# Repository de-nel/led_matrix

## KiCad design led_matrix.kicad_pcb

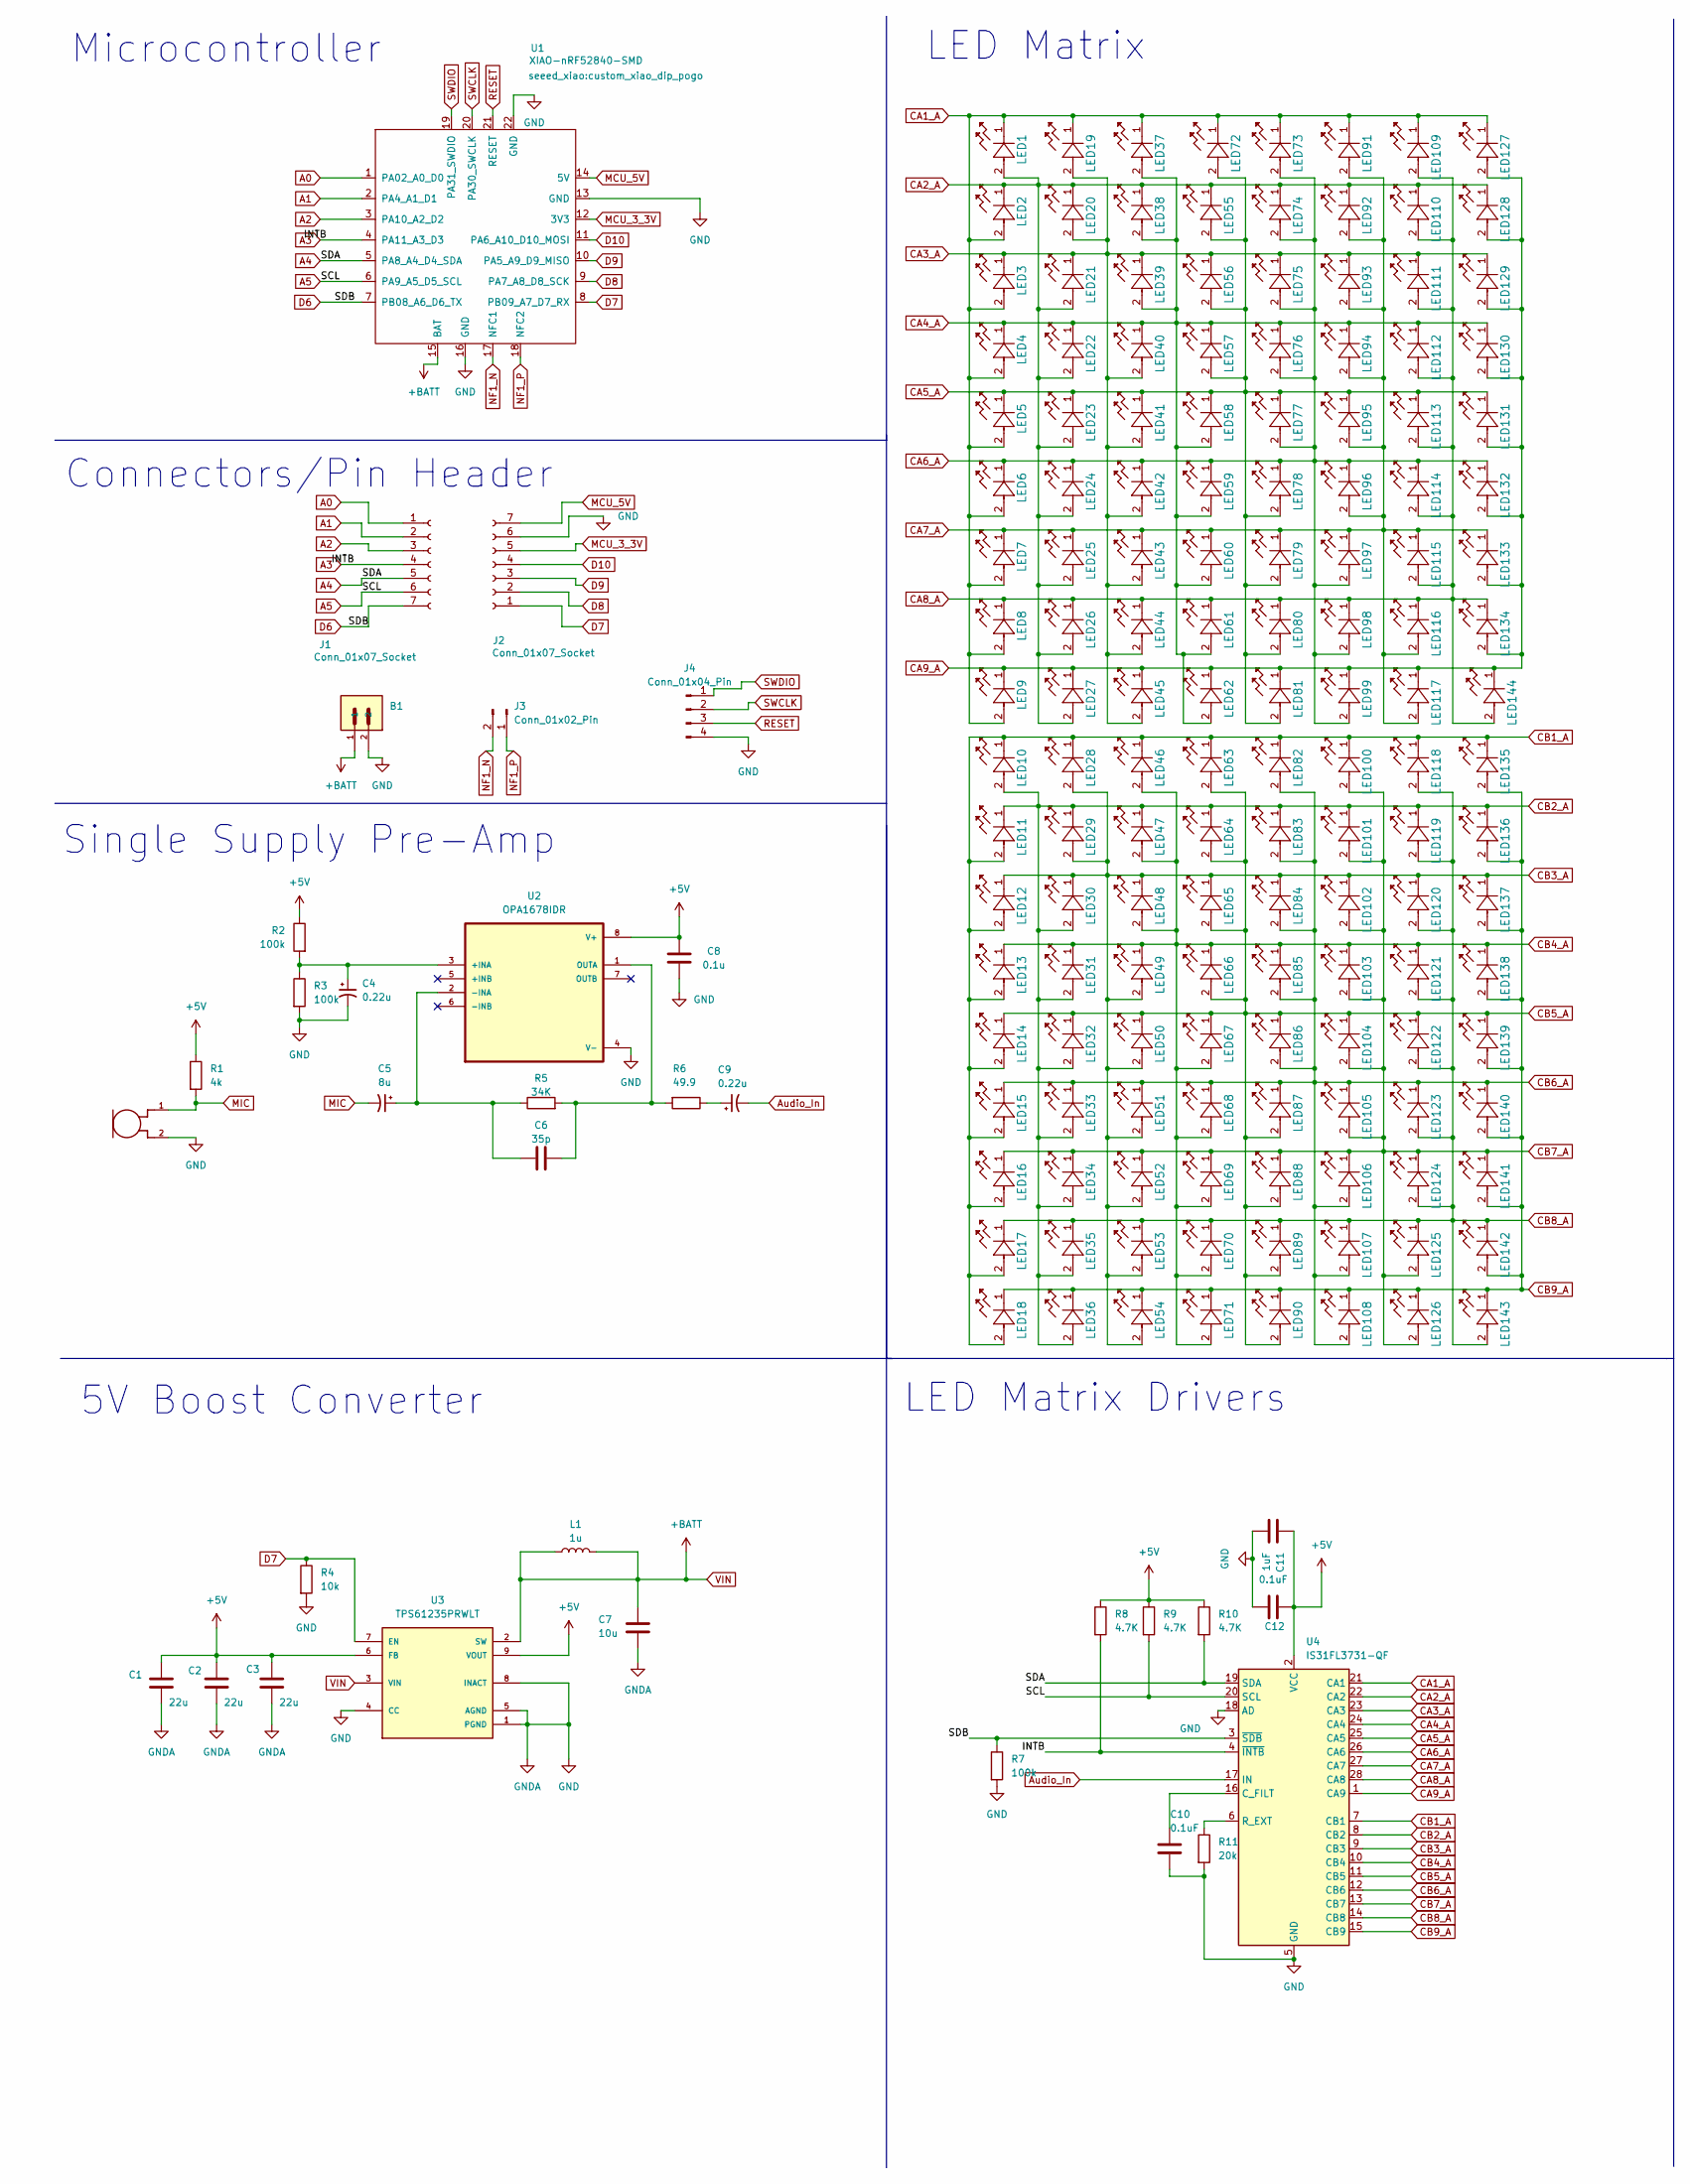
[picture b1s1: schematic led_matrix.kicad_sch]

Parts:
B1: S2B-PH-SM4-TB; JST_S2B-PH-SM4-TB
C1, C2, C3: 22u; C_0805_2012Metric_Pad1.18x1.45mm_HandSolder
C4, C9: 0.22u; CP_EIA-2012-15_AVX-P_HandSolder
C5: 8u; CP_EIA-2012-15_AVX-P_HandSolder
C6: 35p; C_0805_2012Metric_Pad1.18x1.45mm_HandSolder
C7: 10u; C_0805_2012Metric_Pad1.18x1.45mm_HandSolder
C8: 0.1u; C_0805_2012Metric_Pad1.18x1.45mm_HandSolder
C10, C12: 0.1uF; C_0805_2012Metric_Pad1.18x1.45mm_HandSolder
C11: 1uF; C_0805_2012Metric_Pad1.18x1.45mm_HandSolder
J1, J2: Conn_01x07_Socket; PinSocket_1x07_P2.54mm_Vertical_SMD_Pin1Left
J3: Conn_01x02_Pin; SolderWire-0.25sqmm_1x02_P4.5mm_D0.65mm_OD2mm
J4: Conn_01x04_Pin; PinHeader_1x04_P2.54mm_Vertical_SMD_Pin1Left
L1: 1u; L_0805_2012Metric_Pad1.15x1.40mm_HandSolder
LED1, LED2, LED3, LED4, LED5, LED6, LED7, LED8, LED9, LED10, LED11, LED12, LED13, LED14, LED15, LED16, LED17, LED18, LED19, LED20, LED21, LED22, LED23, LED24, LED25, LED26, LED27, LED28, LED29, LED30, LED31, LED32, LED33, LED34, LED35, LED36, LED37, LED38, LED39, LED40, LED41, LED42, LED43, LED44, LED45, LED46, LED47, LED48, LED49, LED50, LED51, LED52, LED53, LED54, LED55, LED56, LED57, LED58, LED59, LED60, LED61, LED62, LED63, LED64, LED65, LED66, LED67, LED68, LED69, LED70, LED71, LED72, LED73, LED74, LED75, LED76, LED77, LED78, LED79, LED80, LED81, LED82, LED83, LED84, LED85, LED86, LED87, LED88, LED89, LED90, LED91, LED92, LED93, LED94, LED95, LED96, LED97, LED98, LED99, LED100, LED101, LED102, LED103, LED104, LED105, LED106, LED107, LED108, LED109, LED110, LED111, LED112, LED113, LED114, LED115, LED116, LED117, LED118, LED119, LED120, LED121, LED122, LED123, LED124, LED125, LED126, LED127, LED128, LED129, LED130, LED131, LED132, LED133, LED134, LED135, LED136, LED137, LED138, LED139, LED140, LED141, LED142, LED143, LED144: IN-S85AT5B; LED_IN-S85AT5B
M1: CMA-4544PF-W; MIC_CMA-4544PF-W
R1: 4k; R_0805_2012Metric_Pad1.20x1.40mm_HandSolder
R2, R3, R7: 100k; R_0805_2012Metric_Pad1.20x1.40mm_HandSolder
R4: 10k; R_0805_2012Metric_Pad1.20x1.40mm_HandSolder
R5: 34K; LED_0805_2012Metric_Pad1.15x1.40mm_HandSolder
R6: 49.9; R_0805_2012Metric_Pad1.20x1.40mm_HandSolder
R8, R9, R10: 4.7K; R_0805_2012Metric_Pad1.20x1.40mm_HandSolder
R11: 20k; R_0805_2012Metric_Pad1.20x1.40mm_HandSolder
U1: XIAO-nRF52840-SMD; custom_xiao_dip_pogo
U2: OPA1678IDR; SOIC127P599X175-8N
U3: TPS61235PRWLT; CONV_TPS61235PRWLT
U4: IS31FL3731-QF; QFN40P400X400X80-29N-D

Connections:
+5V: C1.1, C2.1, C3.1, C8.1, C11.1, C12.1, R1.1, R2.1, R8.1, R9.1, R10.1, U2.8 (V+), U3.6 (FB), U3.9 (VOUT), U4.2 (VCC)
A0: J1.1, U1.1 (PA02_A0_D0)
A1: J1.2, U1.2 (PA4_A1_D1)
A2: J1.3, U1.3 (PA10_A2_D2)
A3: J1.4, R8.2, U1.4 (PA11_A3_D3), U4.4 (~INTB)
A4: J1.5, R10.2, U1.5 (PA8_A4_D4_SDA), U4.19 (SDA)
A5: J1.6, R9.2, U1.6 (PA9_A5_D5_SCL), U4.20 (SCL)
Audio_In: C9.2, U4.17 (IN)
CA1_A: LED1.1, LED2.2, LED3.2, LED4.2, LED5.2, LED6.2, LED7.2, LED8.2, LED9.2, LED19.1, LED37.1, LED72.1, LED73.1, LED91.1, LED109.1, LED127.1, U4.21 (CA1)
CA2_A: LED1.2, LED2.1, LED20.1, LED21.2, LED22.2, LED23.2, LED24.2, LED25.2, LED26.2, LED27.2, LED38.1, LED55.1, LED74.1, LED92.1, LED110.1, LED128.1, U4.22 (CA2)
CA3_A: LED3.1, LED19.2, LED20.2, LED21.1, LED39.1, LED40.2, LED41.2, LED42.2, LED43.2, LED44.2, LED45.2, LED56.1, LED75.1, LED93.1, LED111.1, LED129.1, U4.23 (CA3)
CA4_A: LED4.1, LED22.1, LED37.2, LED38.2, LED39.2, LED40.1, LED57.1, LED58.2, LED59.2, LED60.2, LED61.2, LED62.2, LED76.1, LED94.1, LED112.1, LED130.1, U4.24 (CA4)
CA5_A: LED5.1, LED23.1, LED41.1, LED55.2, LED56.2, LED57.2, LED58.1, LED72.2, LED77.1, LED78.2, LED79.2, LED80.2, LED81.2, LED95.1, LED113.1, LED131.1, U4.25 (CA5)
CA6_A: LED6.1, LED24.1, LED42.1, LED59.1, LED73.2, LED74.2, LED75.2, LED76.2, LED77.2, LED78.1, LED96.1, LED97.2, LED98.2, LED99.2, LED114.1, LED132.1, U4.26 (CA6)
CA7_A: LED7.1, LED25.1, LED43.1, LED60.1, LED79.1, LED91.2, LED92.2, LED93.2, LED94.2, LED95.2, LED96.2, LED97.1, LED115.1, LED116.2, LED117.2, LED133.1, U4.27 (CA7)
CA8_A: LED8.1, LED26.1, LED44.1, LED61.1, LED80.1, LED98.1, LED109.2, LED110.2, LED111.2, LED112.2, LED113.2, LED114.2, LED115.2, LED116.1, LED134.1, LED144.2, U4.28 (CA8)
CA9_A: LED9.1, LED27.1, LED45.1, LED62.1, LED81.1, LED99.1, LED117.1, LED127.2, LED128.2, LED129.2, LED130.2, LED131.2, LED132.2, LED133.2, LED134.2, LED144.1, U4.1 (CA9)
CB1_A: LED10.1, LED11.2, LED12.2, LED13.2, LED14.2, LED15.2, LED16.2, LED17.2, LED18.2, LED28.1, LED46.1, LED63.1, LED82.1, LED100.1, LED118.1, LED135.1, U4.7 (CB1)
CB2_A: LED10.2, LED11.1, LED29.1, LED30.2, LED31.2, LED32.2, LED33.2, LED34.2, LED35.2, LED36.2, LED47.1, LED64.1, LED83.1, LED101.1, LED119.1, LED136.1, U4.8 (CB2)
CB3_A: LED12.1, LED28.2, LED29.2, LED30.1, LED48.1, LED49.2, LED50.2, LED51.2, LED52.2, LED53.2, LED54.2, LED65.1, LED84.1, LED102.1, LED120.1, LED137.1, U4.9 (CB3)
CB4_A: LED13.1, LED31.1, LED46.2, LED47.2, LED48.2, LED49.1, LED66.1, LED67.2, LED68.2, LED69.2, LED70.2, LED71.2, LED85.1, LED103.1, LED121.1, LED138.1, U4.10 (CB4)
CB5_A: LED14.1, LED32.1, LED50.1, LED63.2, LED64.2, LED65.2, LED66.2, LED67.1, LED86.1, LED87.2, LED88.2, LED89.2, LED90.2, LED104.1, LED122.1, LED139.1, U4.11 (CB5)
CB6_A: LED15.1, LED33.1, LED51.1, LED68.1, LED82.2, LED83.2, LED84.2, LED85.2, LED86.2, LED87.1, LED105.1, LED106.2, LED107.2, LED108.2, LED123.1, LED140.1, U4.12 (CB6)
CB7_A: LED16.1, LED34.1, LED52.1, LED69.1, LED88.1, LED100.2, LED101.2, LED102.2, LED103.2, LED104.2, LED105.2, LED106.1, LED124.1, LED125.2, LED126.2, LED141.1, U4.13 (CB7)
CB8_A: LED17.1, LED35.1, LED53.1, LED70.1, LED89.1, LED107.1, LED118.2, LED119.2, LED120.2, LED121.2, LED122.2, LED123.2, LED124.2, LED125.1, LED142.1, LED143.2, U4.14 (CB8)
CB9_A: LED18.1, LED36.1, LED54.1, LED71.1, LED90.1, LED108.1, LED126.1, LED135.2, LED136.2, LED137.2, LED138.2, LED139.2, LED140.2, LED141.2, LED142.2, LED143.1, U4.15 (CB9)
D6: J1.7, R7.1, U1.7 (PB08_A6_D6_TX), U4.3 (~SDB)
D7: J2.1, R4.1, U1.8 (PB09_A7_D7_RX), U3.7 (EN)
D8: J2.2, U1.9 (PA7_A8_D8_SCK)
D9: J2.3, U1.10 (PA5_A9_D9_MISO)
D10: J2.4, U1.11 (PA6_A10_D10_MOSI)
GND: B1.2, C1.2, C2.2, C3.2, C4.2, C7.2, C8.2, C10.2, C11.2, C12.2, J2.6, J4.4, M1.2, R3.2, R4.2, R7.2, R11.2, U1.13 (GND), U1.16 (GND), U1.22 (GND), U2.4 (V-), U3.1 (PGND), U3.4 (CC), U3.5 (AGND), U3.8 (INACT), U4.5 (GND), U4.18 (AD), U4.29 (GND)
MCU_3_3V: J2.5, U1.12 (3V3)
MCU_5V: J2.7, U1.14 (5V)
MIC: C5.2, M1.1, R1.2
NF1_N: J3.2, U1.17 (NFC1)
NF1_P: J3.1, U1.18 (NFC2)
unnamed: C9.1, R6.1
unnamed: C4.1, R2.2, R3.1, U2.3 (+INA)
unnamed: C5.1, C6.1, R5.1, U2.2 (-INA)
unnamed: C6.2, R5.2, R6.2, U2.1 (OUTA)
unnamed: C10.1, U4.16 (C_FILT)
unnamed: R11.1, U4.6 (R_EXT)
RESET: J4.3, U1.21 (RESET)
SWCLK: J4.2, U1.20 (PA30_SWCLK)
SWDIO: J4.1, U1.19 (PA31_SWDIO)
VIN: B1.1, C7.1, L1.1, L1.2, U1.15 (BAT), U3.2 (SW), U3.3 (VIN)

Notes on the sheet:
LED Matrix Drivers
LED Matrix
Microcontroller
Single Supply Pre-Amp
Connectors/Pin Header
5V Boost Converter

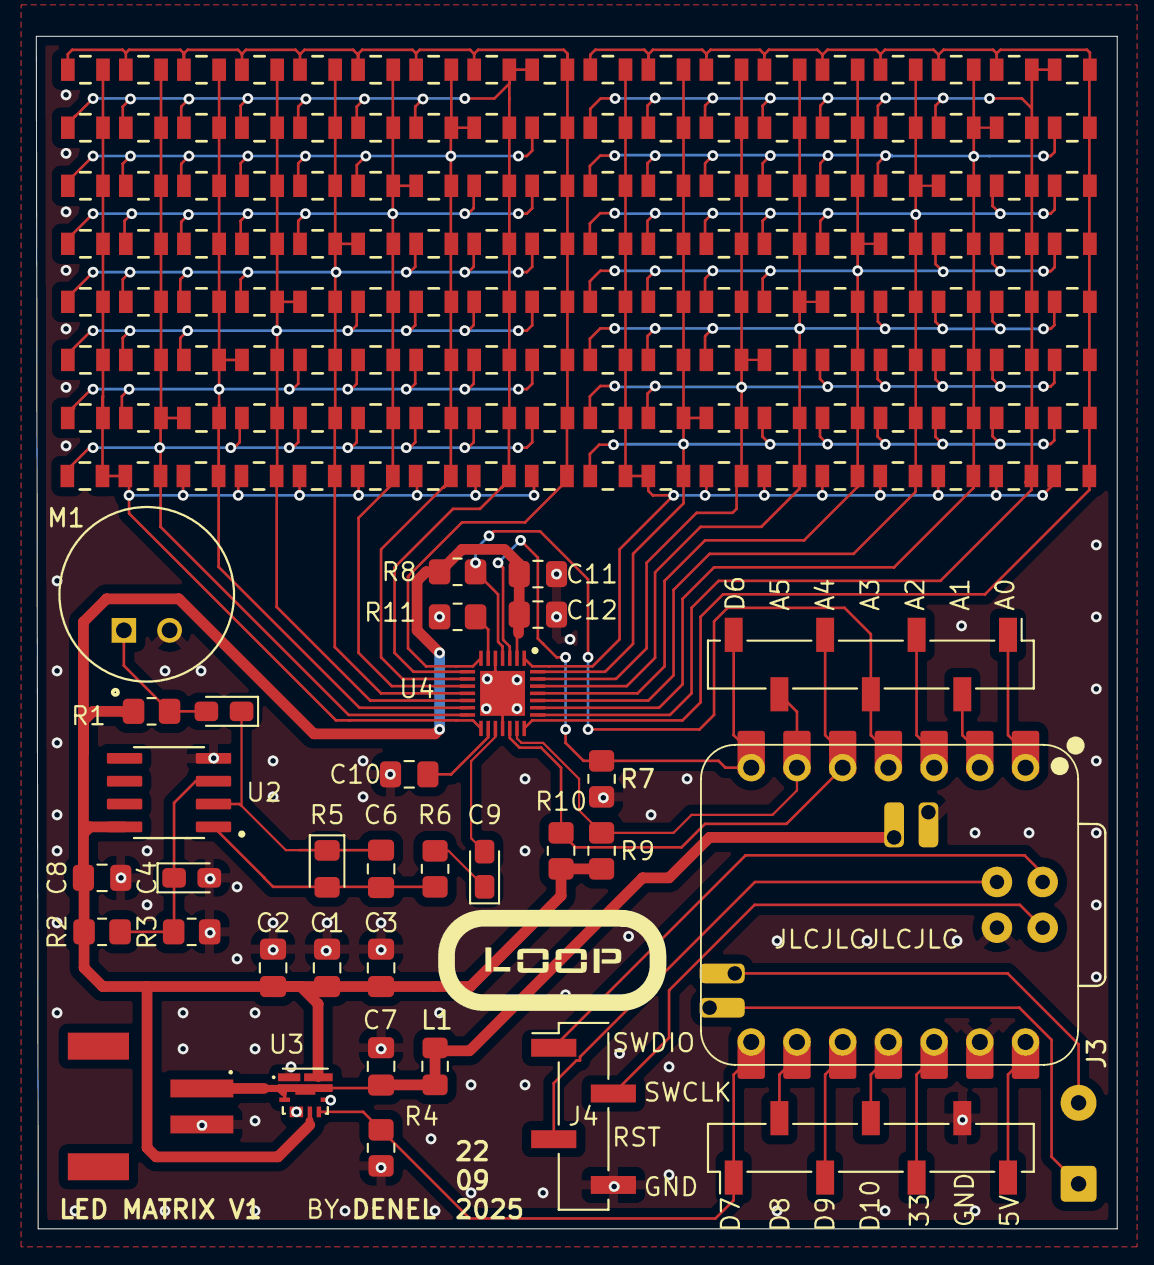
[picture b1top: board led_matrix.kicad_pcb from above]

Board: 2 copper layers, 60.1 x 66.2 mm, 178 parts (0 on the bottom side), 47 nets.

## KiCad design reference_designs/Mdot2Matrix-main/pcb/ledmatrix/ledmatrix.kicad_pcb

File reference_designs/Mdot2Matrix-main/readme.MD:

# M.2 LED Matrix

## Goal

This project is a showcase and starting point for M.2 PCIe hardware. The interface chip CH382 was used to inteface between the first PCIe lane and the CH32V208 MCU over UART.
Check out the [versionProject video](https://youtu.be/yxVQkL01FD4)

## State

RTS and DTR control flow signals are used to put the MCU into bootloader. !Caution This version is not working correctly as the signals are flipped on boot etc. Here is an updated [version](https://www.falstad.com/circuit/circuitjs.html?ctz=CQAgjCAMB0l3BWcAOaAmA7MgnGB-kA2MAFgwTREMJCQUloFMBaMMAKACcQS4QBmSCVoYag4QzDxIXETWaFhCUQKFQQaaewDmA5MLBj9AygxmaMGtAbTIrw5A2EAlACoBldhZ4k7C4SS+IKxglMIAhAAirs7sAO56wv4+fopQsvzGIZSZSWmSWt5o1sFBxUnYNMLRsc6JwWw5WaQS6rwC0PzqZtAIXpCWgXYtKSCVPCAAQgDy067mA1QIYmqEyxrrwgByzu6uOvXWDLkbNGYZFKV2tn5BBfAXlKHXyMO26lIPAC4Cl8xBJ3+dkkUF69EIkAhyDAlTQFAwlhgCEqhFwkLQhGscOIqhAABNGAAzACGAFcADZfdg-fiXZ71ekgpH4NBgZC2QykBGhUEIEjUQg4fS5MhdQT4olkynxBmBUYjGQJcrgd7K8TpBJDYJpZTyfLsAAy4DlQLG8ju4BAJPJAGdGB0ujIjSN6eNGZbrXaHekALIgDCaVTCUR2dWSaBrdh4+xBnh8dVPLbKUIZYxHBnYUzgaQyP1aka+SRy8ORzVBZJa-VluxpE5V+q14yNdI241JMolU1mK3E22MR7gMR-C2fODsVsu1Uld0MT39pXT1WvFXAgcwnJ0973McJXWxtYrCTsfiCpaHs8CE-dY+n-Ny-Mqc4JA+xgPHNQyVtv1+Bk-Aj29naBzfn+-q-sY5wAMZyLGe6gQYLCWGgsCQLgoSspg+jIBgeCgnAEAyLocGnnBEEahoy6msqXYyrSTxGAYZy0Vk-BNIx5EnCMnGZhxdI8dxpjsAAHhRlisMctLBIMKogAAqj6AASbBbOwABGGg4dqdi8AwgYyCJNyDkg-BXoY2kyfJSlgCp6mYBAUiDHwMJIDIAD2YwgP+JBSKY0B4JiLkoXA2CiMscLqJQ2ACFMszzOw7lSJ5bQ+bQeHwCFB7hbp2bRTsezxf6SVOClgUERohVdDUBVdF5JWgmVOTRW4nhAA)

In general the interface chip draws 170mA which puts the little LDO at it's limit. The thermals are terrible. Would not recomment to use this setup for a commercial project without a severe refinement.

## Tools

The firmware can be uploaded via the [wch web isp](https://github.com/basilhussain/wch-web-isp)

The code is written with the [MounRiver Studio](http://www.mounriver.com/download)

Node.js is required to run the websocket server

## Vibe coding

The majority of the web tool and the server are generated with ChatGPT which was trained on dacades of mine and your public code.

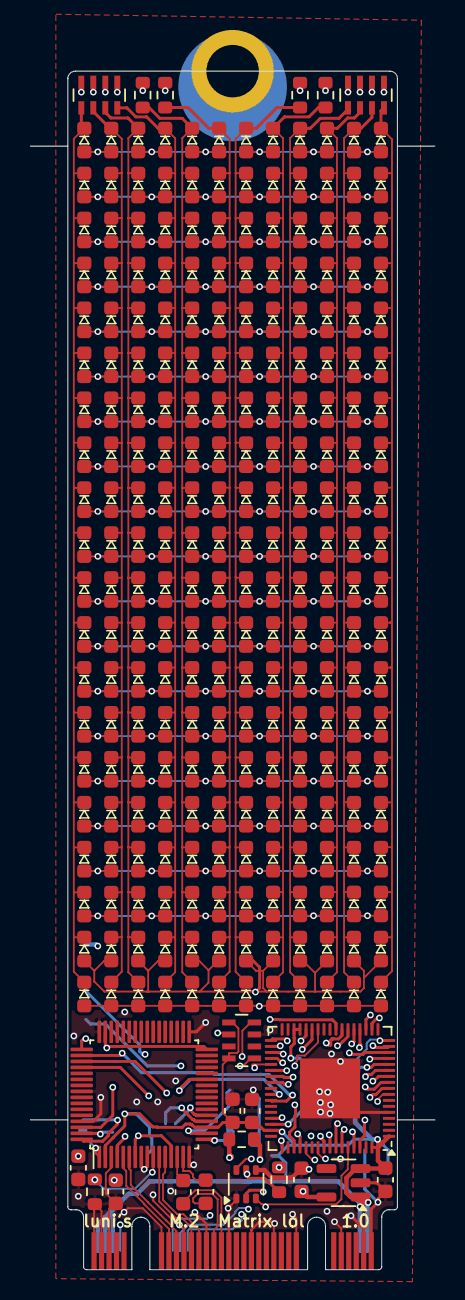
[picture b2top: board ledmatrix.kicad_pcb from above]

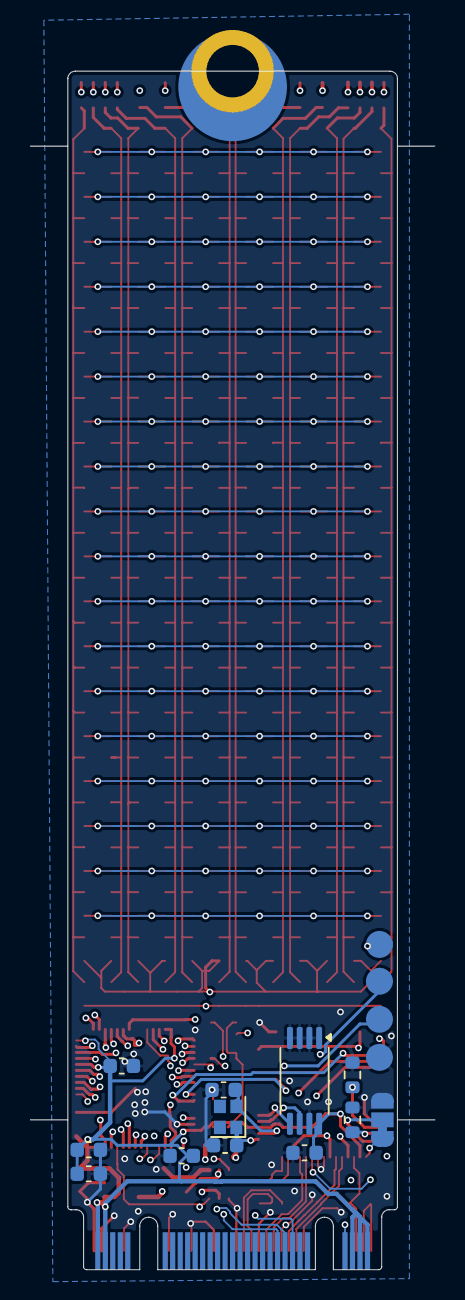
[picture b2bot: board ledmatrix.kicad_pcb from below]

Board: 4 copper layers, 27.0 x 80.0 mm, 276 parts (13 on the bottom side), 77 nets.

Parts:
C1, C2, C3, C10, C12, C15, C21, C22, C23, C24, C25: 100n; C_0603_1608Metric
C8, C11: 10u; C_0603_1608Metric
C16, C17: 27p; C_0603_1608Metric
D121, D122, D123, D124, D125, D126, D127, D128, D129, D130, D131, D132, D133, D134, D135, D136, D137, D138, D139, D140, D141, D142, D143, D144, D145, D146, D147, D148, D149, D150, D151, D152, D153, D154, D155, D156, D157, D158, D159, D160, D161, D162, D163, D164, D165, D166, D167, D168, D169, D170, D171, D172, D173, D174, D175, D176, D177, D178, D179, D180, D181, D182, D183, D184, D185, D186, D187, D188, D189, D190, D191, D192, D193, D194, D195, D196, D197, D198, D199, D200, D201, D202, D203, D204, D205, D206, D207, D208, D209, D210, D211, D212, D213, D214, D215, D216, D217, D218, D219, D220, D221, D222, D223, D224, D225, D226, D227, D228, D229, D230, D231, D232, D233, D234, D235, D236, D237, D238, D239, D240, D241, D242, D243, D244, D245, D246, D247, D248, D249, D250, D251, D252, D253, D254, D255, D256, D257, D258, D259, D260, D261, D262, D263, D264, D265, D266, D267, D268, D269, D270, D271, D272, D273, D274, D275, D276, D277, D278, D279, D280, D281, D282, D283, D284, D285, D286, D287, D288, D289, D290, D291, D292, D293, D294, D295, D296, D297, D298, D299, D300, D301, D302, D303, D304, D305, D306, D307, D308, D309, D310, D311, D312, D313, D314, D315, D316, D317, D318, D319, D320, D321, D322, D323, D324, D325, D326, D327, D328, D329, D330, D331, D332, D333, D334, D335, D336, D337, D338, D339, D340, D341, D342, D343, D344, D345, D346, D347, D348, D349, D350, D351, D352, D353, D354, D355, D356, D357, D358, D359, D360: LEDdiag0603; LED_0603
JP2: Jumper_3_Bridged12; SolderJumper-3_P1.3mm_Bridged12_RoundedPad1.0x1.5mm
Q1: UMH3N; SOT-363_SC-70-6
R8, R13, R14, R15, R16: 1k; R_0603_1608Metric
R9, R10, R11: 0; R_0603_1608Metric
R12: 12k; R_0603_1608Metric
RN5, RN6: 1k; R_Array_Concave_4x0603
RN8: 10k; R_Array_Concave_4x0603
TP1: TestPoint; Testpoint4
U1: CH382; LQFP-64_7x7mm_P0.4mm
U2: M.2-B+M-KEY-PCIe; M.2-B+M-KEY 2280
U4: M24C02-FDW; TSSOP-8_4.4x3mm_P0.65mm
U5: QFN-68-1EP_8x8mm_P0.4mm_EP4x4mm
U6: AP2112K-1.8; SOT-23-5
Y1: 22.1184MHz; Crystal_SMD_2016-4Pin_2.0x1.6mm

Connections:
1V8: C10.2, C11.2, R9.1, U1.4 (VCC18), U1.32 (VCC18), U1.47 (VCC18), U6.5 (VOUT)
1V8A: C12.2, R9.2, U1.7 (VCC18A), U1.13 (VCC18A)
/BOOT1: R8.2, U5.28 (PB2/BOOT1)
/CKSEL: JP2.2 (C), U1.64 (CKSEL)
/CLKREQ#: RN8.2 (R2.1), U2.P$52 (CLKREQ#)
/CLK_32k: U2.P$68 (SUSCLK(32kHz)), U5.58 (PB3)
/DTR: Q1.2 (B1), U1.52 (DTR0)
/PECK+: U1.5 (PECK+), U2.P$55 (REFCLK+)
/PECK-: U1.6 (PECK-), U2.P$53 (REFCLK-)
/PER+: U1.11 (PER+), U2.P$49 (PER0+)
/PER-: U1.12 (PER-), U2.P$47 (PER0-)
/PET+: C2.2, U1.15 (PET+)
/PET-: C1.2, U1.14 (PET-)
/RST#: JP2.1 (A), U1.1 (PERST#), U2.P$50 (PERST#)
/RST_CH32#: Q1.6 (C1), RN8.8 (R1.2), U5.8 (NRST)
/RTS: Q1.5 (B2), R8.1, U1.51 (RTS0)
/RX: U1.27 (RXD0), U5.44 (PA9)
/TX: U1.50 (TXD0), U5.45 (PA10)
/WAKE#: U2.P$54 (PEWAKE#), U5.56 (PC12)
BOOT0: Q1.3 (C2), RN8.5 (R4.2), U5.63 (BOOT0)
GND: C3.1, C8.1, C10.1, C11.1, C12.1, C15.1, C16.2, C17.2, C21.2, C22.2, C23.2, C24.2, C25.2, JP2.3 (B), Q1.1 (E1), Q1.4 (E2), R10.2, R11.2, R12.2, RN8.7 (R2.2), TP1.1, U1.3 (GND), U1.8 (GND), U1.9 (GND), U1.16 (GND), U1.33 (GND), U1.48 (GND), U1.56 (GND), U1.61 (GND), U2.P$1 (CONFIG3/GND), U2.P$3 (GND), U2.P$9 (GND), U2.P$21 (CONFIG_0/GND), U2.P$27 (GND), U2.P$33 (GND), U2.P$39 (GND), U2.P$45 (GND), U2.P$51 (GND), U2.P$57 (GND), U2.P$71 (GND), U2.P$73 (GND), U2.P$75 (CONFIG_2/GND), U4.1 (E0), U4.2 (E1), U4.3 (E2), U4.4 (VSS), U4.7 (~WC), U5.5 (VSSA), U5.49 (VSS_2), U5.69 (VSS), U6.2 (GND)
unnamed: D121.1 (K), D133.1 (K), D145.1 (K), D157.1 (K), D169.1 (K), D181.1 (K), D193.1 (K), D205.1 (K), D217.1 (K), D229.1 (K), D241.1 (K), D253.1 (K), D265.1 (K), D277.1 (K), D289.1 (K), D301.1 (K), D313.1 (K), D325.1 (K), D337.1 (K), D349.1 (K), RN5.4 (R4.1)
unnamed: D122.1 (K), D134.1 (K), D146.1 (K), D158.1 (K), D170.1 (K), D182.1 (K), D194.1 (K), D206.1 (K), D218.1 (K), D230.1 (K), D242.1 (K), D254.1 (K), D266.1 (K), D278.1 (K), D290.1 (K), D302.1 (K), D314.1 (K), D326.1 (K), D338.1 (K), D350.1 (K), RN5.3 (R3.1)
unnamed: D123.1 (K), D135.1 (K), D147.1 (K), D159.1 (K), D171.1 (K), D183.1 (K), D195.1 (K), D207.1 (K), D219.1 (K), D231.1 (K), D243.1 (K), D255.1 (K), D267.1 (K), D279.1 (K), D291.1 (K), D303.1 (K), D315.1 (K), D327.1 (K), D339.1 (K), D351.1 (K), RN5.2 (R2.1)
unnamed: D124.1 (K), D136.1 (K), D148.1 (K), D160.1 (K), D172.1 (K), D184.1 (K), D196.1 (K), D208.1 (K), D220.1 (K), D232.1 (K), D244.1 (K), D256.1 (K), D268.1 (K), D280.1 (K), D292.1 (K), D304.1 (K), D316.1 (K), D328.1 (K), D340.1 (K), D352.1 (K), RN5.1 (R1.1)
unnamed: D125.1 (K), D137.1 (K), D149.1 (K), D161.1 (K), D173.1 (K), D185.1 (K), D197.1 (K), D209.1 (K), D221.1 (K), D233.1 (K), D245.1 (K), D257.1 (K), D269.1 (K), D281.1 (K), D293.1 (K), D305.1 (K), D317.1 (K), D329.1 (K), D341.1 (K), D353.1 (K), R13.1
unnamed: D126.1 (K), D138.1 (K), D150.1 (K), D162.1 (K), D174.1 (K), D186.1 (K), D198.1 (K), D210.1 (K), D222.1 (K), D234.1 (K), D246.1 (K), D258.1 (K), D270.1 (K), D282.1 (K), D294.1 (K), D306.1 (K), D318.1 (K), D330.1 (K), D342.1 (K), D354.1 (K), R14.1
unnamed: D127.1 (K), D139.1 (K), D151.1 (K), D163.1 (K), D175.1 (K), D187.1 (K), D199.1 (K), D211.1 (K), D223.1 (K), D235.1 (K), D247.1 (K), D259.1 (K), D271.1 (K), D283.1 (K), D295.1 (K), D307.1 (K), D319.1 (K), D331.1 (K), D343.1 (K), D355.1 (K), R15.1
unnamed: D128.1 (K), D140.1 (K), D152.1 (K), D164.1 (K), D176.1 (K), D188.1 (K), D200.1 (K), D212.1 (K), D224.1 (K), D236.1 (K), D248.1 (K), D260.1 (K), D272.1 (K), D284.1 (K), D296.1 (K), D308.1 (K), D320.1 (K), D332.1 (K), D344.1 (K), D356.1 (K), R16.1
unnamed: D129.1 (K), D141.1 (K), D153.1 (K), D165.1 (K), D177.1 (K), D189.1 (K), D201.1 (K), D213.1 (K), D225.1 (K), D237.1 (K), D249.1 (K), D261.1 (K), D273.1 (K), D285.1 (K), D297.1 (K), D309.1 (K), D321.1 (K), D333.1 (K), D345.1 (K), D357.1 (K), RN6.4 (R4.1)
unnamed: D130.1 (K), D142.1 (K), D154.1 (K), D166.1 (K), D178.1 (K), D190.1 (K), D202.1 (K), D214.1 (K), D226.1 (K), D238.1 (K), D250.1 (K), D262.1 (K), D274.1 (K), D286.1 (K), D298.1 (K), D310.1 (K), D322.1 (K), D334.1 (K), D346.1 (K), D358.1 (K), RN6.3 (R3.1)
unnamed: D131.1 (K), D143.1 (K), D155.1 (K), D167.1 (K), D179.1 (K), D191.1 (K), D203.1 (K), D215.1 (K), D227.1 (K), D239.1 (K), D251.1 (K), D263.1 (K), D275.1 (K), D287.1 (K), D299.1 (K), D311.1 (K), D323.1 (K), D335.1 (K), D347.1 (K), D359.1 (K), RN6.2 (R2.1)
unnamed: D132.1 (K), D144.1 (K), D156.1 (K), D168.1 (K), D180.1 (K), D192.1 (K), D204.1 (K), D216.1 (K), D228.1 (K), D240.1 (K), D252.1 (K), D264.1 (K), D276.1 (K), D288.1 (K), D300.1 (K), D312.1 (K), D324.1 (K), D336.1 (K), D348.1 (K), D360.1 (K), RN6.1 (R1.1)
unnamed: R11.1, U1.62 (MDPRT#)
unnamed: R10.1, U1.63 (MDSEL)
unnamed: R12.1, U1.10 (RREF)
unnamed: U1.20 (SCL), U4.6 (SCL)
unnamed: U1.21 (SDA), U4.5 (SDA)
unnamed: C16.1, U1.18 (XI), Y1.2
unnamed: C17.1, U1.17 (XO), Y1.1
unnamed: C2.1, U2.P$43 (PET0+)
unnamed: C1.1, U2.P$41 (PET0-)
PA0: D121.2 (A), D122.2 (A), D123.2 (A), D124.2 (A), D125.2 (A), D126.2 (A), D127.2 (A), D128.2 (A), D129.2 (A), D130.2 (A), D131.2 (A), D132.2 (A), U5.14 (PA0/WKUP/ADC0)
PA1: D133.2 (A), D134.2 (A), D135.2 (A), D136.2 (A), D137.2 (A), D138.2 (A), D139.2 (A), D140.2 (A), D141.2 (A), D142.2 (A), D143.2 (A), D144.2 (A), U5.15 (PA1/ADC1)
PA2: D145.2 (A), D146.2 (A), D147.2 (A), D148.2 (A), D149.2 (A), D150.2 (A), D151.2 (A), D152.2 (A), D153.2 (A), D154.2 (A), D155.2 (A), D156.2 (A), U5.16 (PA2/ADC2)
PA3: D157.2 (A), D158.2 (A), D159.2 (A), D160.2 (A), D161.2 (A), D162.2 (A), D163.2 (A), D164.2 (A), D165.2 (A), D166.2 (A), D167.2 (A), D168.2 (A), U5.19 (PA3/ADC3)
PA4: D169.2 (A), D170.2 (A), D171.2 (A), D172.2 (A), D173.2 (A), D174.2 (A), D175.2 (A), D176.2 (A), D177.2 (A), D178.2 (A), D179.2 (A), D180.2 (A), U5.20 (PA4/ADC4)
PA5: D181.2 (A), D182.2 (A), D183.2 (A), D184.2 (A), D185.2 (A), D186.2 (A), D187.2 (A), D188.2 (A), D189.2 (A), D190.2 (A), D191.2 (A), D192.2 (A), U5.21 (PA5/ADC5)
PA6: D193.2 (A), D194.2 (A), D195.2 (A), D196.2 (A), D197.2 (A), D198.2 (A), D199.2 (A), D200.2 (A), D201.2 (A), D202.2 (A), D203.2 (A), D204.2 (A), U5.22 (PA6/ADC6)
PA7: D205.2 (A), D206.2 (A), D207.2 (A), D208.2 (A), D209.2 (A), D210.2 (A), D211.2 (A), D212.2 (A), D213.2 (A), D214.2 (A), D215.2 (A), D216.2 (A), U5.23 (PA7/ADC7)
PB4: D217.2 (A), D218.2 (A), D219.2 (A), D220.2 (A), D221.2 (A), D222.2 (A), D223.2 (A), D224.2 (A), D225.2 (A), D226.2 (A), D227.2 (A), D228.2 (A), U5.59 (PB4)
PB5: D229.2 (A), D230.2 (A), D231.2 (A), D232.2 (A), D233.2 (A), D234.2 (A), D235.2 (A), D236.2 (A), D237.2 (A), D238.2 (A), D239.2 (A), D240.2 (A), U5.60 (PB5)
PB6: D241.2 (A), D242.2 (A), D243.2 (A), D244.2 (A), D245.2 (A), D246.2 (A), D247.2 (A), D248.2 (A), D249.2 (A), D250.2 (A), D251.2 (A), D252.2 (A), U5.61 (PB6/USB2DM)
PB7: D253.2 (A), D254.2 (A), D255.2 (A), D256.2 (A), D257.2 (A), D258.2 (A), D259.2 (A), D260.2 (A), D261.2 (A), D262.2 (A), D263.2 (A), D264.2 (A), U5.62 (PB7/USB2DP)
PB8: D265.2 (A), D266.2 (A), D267.2 (A), D268.2 (A), D269.2 (A), D270.2 (A), D271.2 (A), D272.2 (A), D273.2 (A), D274.2 (A), D275.2 (A), D276.2 (A), U5.64 (PB8)
PB9: D277.2 (A), D278.2 (A), D279.2 (A), D280.2 (A), D281.2 (A), D282.2 (A), D283.2 (A), D284.2 (A), D285.2 (A), D286.2 (A), D287.2 (A), D288.2 (A), U5.65 (PB9)
PB10: D289.2 (A), D290.2 (A), D291.2 (A), D292.2 (A), D293.2 (A), D294.2 (A), D295.2 (A), D296.2 (A), D297.2 (A), D298.2 (A), D299.2 (A), D300.2 (A), U5.29 (PB10)
PB11: D301.2 (A), D302.2 (A), D303.2 (A), D304.2 (A), D305.2 (A), D306.2 (A), D307.2 (A), D308.2 (A), D309.2 (A), D310.2 (A), D311.2 (A), D312.2 (A), U5.30 (PB11)
PB12: D313.2 (A), D314.2 (A), D315.2 (A), D316.2 (A), D317.2 (A), D318.2 (A), D319.2 (A), D320.2 (A), D321.2 (A), D322.2 (A), D323.2 (A), D324.2 (A), U5.35 (PB12)
PB13: D325.2 (A), D326.2 (A), D327.2 (A), D328.2 (A), D329.2 (A), D330.2 (A), D331.2 (A), D332.2 (A), D333.2 (A), D334.2 (A), D335.2 (A), D336.2 (A), U5.36 (PB13)
PB14: D337.2 (A), D338.2 (A), D339.2 (A), D340.2 (A), D341.2 (A), D342.2 (A), D343.2 (A), D344.2 (A), D345.2 (A), D346.2 (A), D347.2 (A), D348.2 (A), U5.37 (PB14)
PB15: D349.2 (A), D350.2 (A), D351.2 (A), D352.2 (A), D353.2 (A), D354.2 (A), D355.2 (A), D356.2 (A), D357.2 (A), D358.2 (A), D359.2 (A), D360.2 (A), U5.38 (PB15)
PC0: RN5.5 (R4.2), U5.9 (PC0/ADC10)
PC1: RN5.6 (R3.2), U5.10 (PC1/ADC11)
PC2: RN5.7 (R2.2), U5.11 (PC2/ADC12)
PC3: RN5.8 (R1.2), U5.12 (PC3/ADC13)
PC4: R13.2, U5.24 (PC4/ADC14)
PC5: R14.2, U5.25 (PC5/ADC15)
PC6: R15.2, U5.39 (PC6/RXP)
PC7: R16.2, U5.40 (PC7/RXN)
PC8: RN6.5 (R4.2), U5.41 (PC8/TXP)
PC9: RN6.6 (R3.2), U5.42 (PC9/TXN)
PC10: RN6.7 (R2.2), U5.54 (PC10)
PC11: RN6.8 (R1.2), U5.55 (PC11)
SWDCLK: TP1.2, U5.52 (PA14/SWCLK)
SWDIO: TP1.3, U5.48 (PA13/SWDIO)
VCC: C3.2, C8.2, C15.2, C21.1, C22.1, C23.1, C24.1, C25.1, RN8.1 (R1.1), RN8.4 (R4.1), TP1.4, U1.2 (VCC33), U1.19 (VCC33), U1.49 (VCC33), U2.P$2 (3V3), U2.P$4 (3V3), U2.P$70 (3V3), U2.P$72 (3V3), U2.P$74 (3V3), U4.8 (VCC), U5.1 (VBAT), U5.13 (VDDA), U5.17 (VIO_4), U5.31 (VIO_1), U5.32 (VDD_1), U5.50 (VINTA), U5.67 (VIO_3), U5.68 (VDD_3), U6.1 (VIN), U6.3 (EN)

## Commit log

2025-08-13 Initial commit with KiCad project and Digi-Key submodule
2025-08-13 seeed Xaio
2025-08-13 seeed Xiao symbol table
2025-08-14 Add .gitignore for KiCad backups/cache
2025-08-14 Update Git submodules Xiao
2025-08-14 Update KiCad project and schematic
2025-08-14 Add .gitignore for KiCad temp/user files
2025-08-14 Add footprint table, ClipZin connector, and Seeed OPL library
2025-08-14 Vendor Seeed OPL KiCad library (no submodule)
2025-08-14 misc files
2025-09-30 Finished PCB
2025-09-30 .gitignore updated
